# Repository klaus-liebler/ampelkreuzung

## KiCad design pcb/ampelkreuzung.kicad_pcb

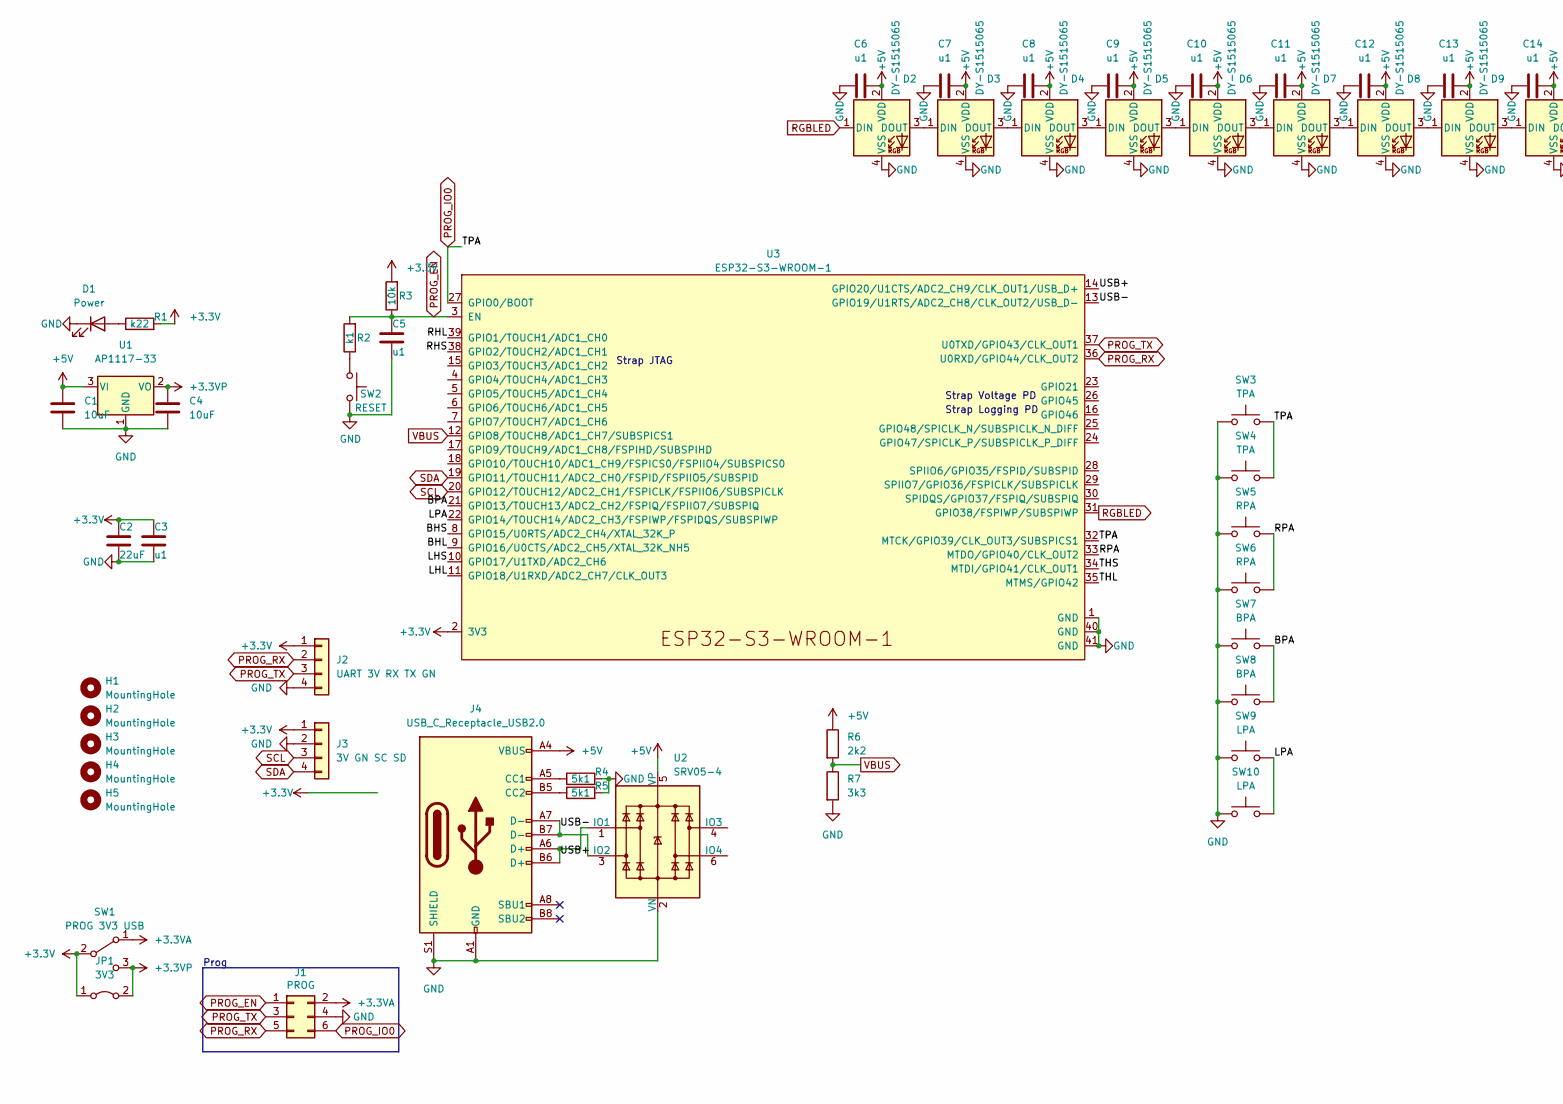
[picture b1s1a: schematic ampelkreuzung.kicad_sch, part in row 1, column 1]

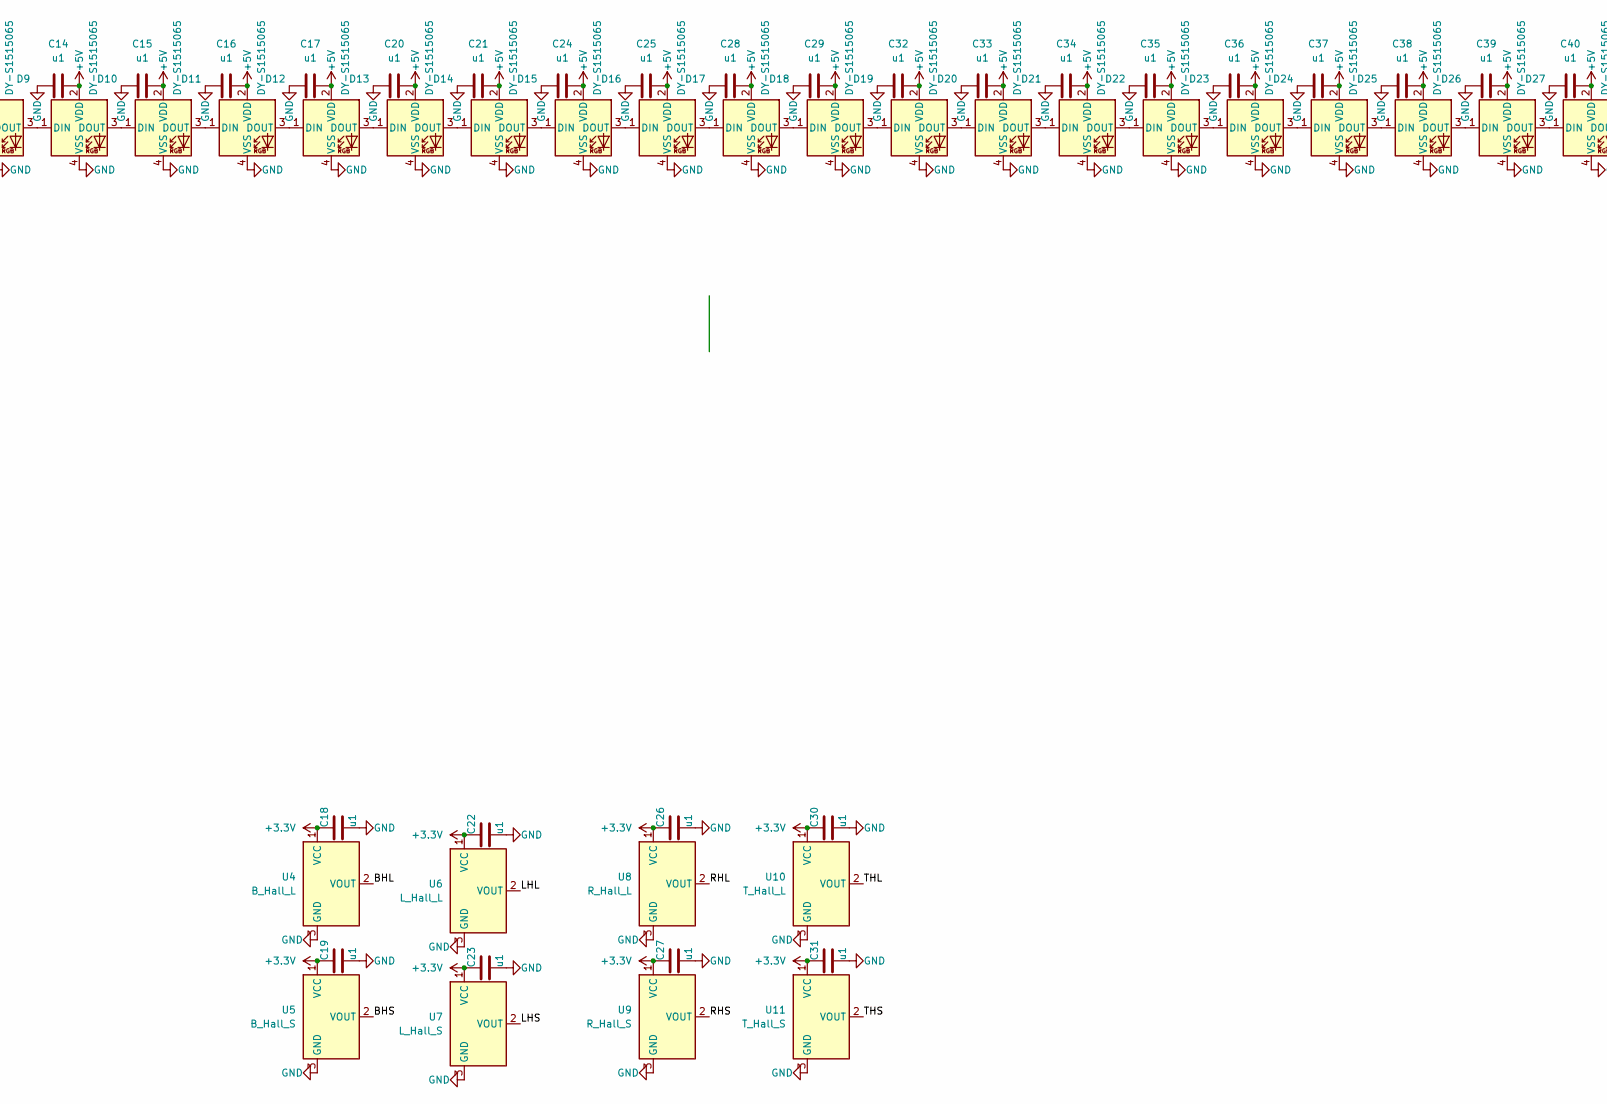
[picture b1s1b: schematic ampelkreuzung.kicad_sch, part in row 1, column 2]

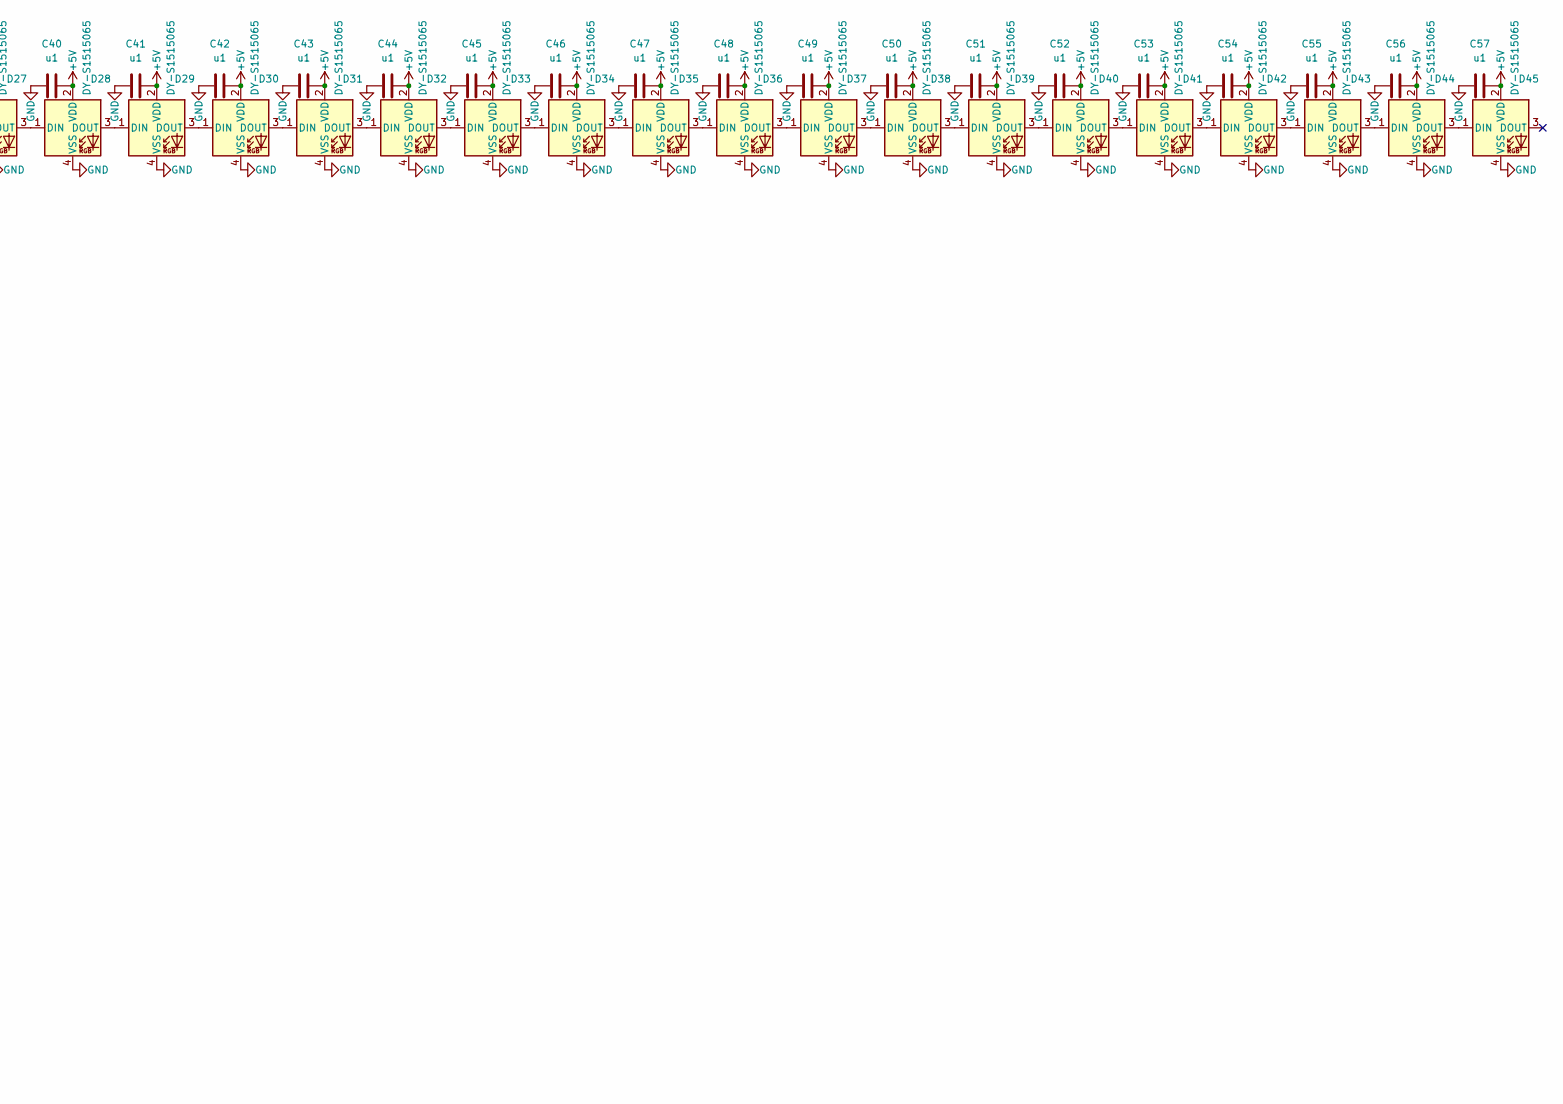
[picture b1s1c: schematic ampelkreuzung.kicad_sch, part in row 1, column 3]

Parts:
C1, C4: 10uF; C_0603_1608Metric
C2: 22uF; C_0603_1608Metric
C3, C5, C6, C7, C8, C9, C10, C11, C12, C13, C14, C15, C16, C17, C18, C19, C20, C21, C22, C23, C24, C25, C26, C27, C28, C29, C30, C31, C32, C33, C34, C35, C36, C37, C38, C39, C40, C41, C42, C43, C44, C45, C46, C47, C48, C49, C50, C51, C52, C53, C54, C55, C56, C57: u1; C_0402_1005Metric
D1: Power; LED_0603_1608Metric
D2, D3, D4, D5, D6, D7, D8, D9, D10, D11, D12, D13, D14, D15, D16, D17, D18, D19, D20, D21, D22, D23, D24, D25, D26, D27, D28, D29, D30, D31, D32, D33, D34, D35, D36, D37, D38, D39, D40, D41, D42, D43, D44, D45: DY-S1515065; LED_0606
H1, H2, H3, H4, H5: MountingHole; MountingHole_3.2mm_M3_DIN965
J1: PROG; IDC_2x03_P1.27mm_Vertical
J2: UART 3V RX TX GN; JST_XH_B4B-XH-A_1x04_P2.50mm_Vertical
J3: 3V GN SC SD; JST_XH_B4B-XH-A_1x04_P2.50mm_Vertical
J4: USB_C_Receptacle_USB2.0; USB_C_Receptacle_HRO_TYPE-C-31-M-12
JP1: 3V3; SolderJumper-2_P1.3mm_Bridged2Bar_RoundedPad1.0x1.5mm
R1: k22; R_0402_1005Metric
R2: k1; R_0402_1005Metric
R3: 10k; R_0402_1005Metric
R4, R5: 5k1; R_0402_1005Metric
R6: 2k2; R_0402_1005Metric
R7: 3k3; R_0402_1005Metric
SW1: PROG 3V3 USB; Switch_SS12D00
SW2: RESET; SW_SPST_TL3342
SW3, SW4: TPA; SW_SPST_TL3342
SW5, SW6: RPA; SW_SPST_TL3342
SW7, SW8: BPA; SW_SPST_TL3342
SW9, SW10: LPA; SW_SPST_TL3342
U1: AP1117-33; SOT-223-3_TabPin2
U2: SRV05-4; SOT-23-6
U3: ESP32-S3-WROOM-1
U4: B_Hall_L; SOT-23_smaller_withoutSilkscreen
U5: B_Hall_S; SOT-23_smaller_withoutSilkscreen
U6: L_Hall_L; SOT-23_smaller_withoutSilkscreen
U7: L_Hall_S; SOT-23_smaller_withoutSilkscreen
U8: R_Hall_L; SOT-23_smaller_withoutSilkscreen
U9: R_Hall_S; SOT-23_smaller_withoutSilkscreen
U10: T_Hall_L; SOT-23_smaller_withoutSilkscreen
U11: T_Hall_S; SOT-23_smaller_withoutSilkscreen

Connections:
+3.3V: C2.1, C3.2, C18.2, C19.2, C22.2, C23.2, C26.2, C27.2, C30.2, C31.2, J2.1, J3.1, JP1.1 (A), R1.2, R3.2, SW1.2 (B), U3.2 (3V3), U4.1 (VCC), U5.1 (VCC), U6.1 (VCC), U7.1 (VCC), U8.1 (VCC), U9.1 (VCC), U10.1 (VCC), U11.1 (VCC)
+3.3VA: J1.2, SW1.1 (A)
+3.3VP: C4.1, JP1.2 (B), SW1.3 (C), U1.2 (VO)
+5V: C1.1, C6.2, C7.2, C8.2, C9.2, C10.2, C11.2, C12.2, C13.2, C14.2, C15.2, C16.2, C17.2, C20.2, C21.2, C24.2, C25.2, C28.2, C29.2, C32.2, C33.2, C34.2, C35.2, C36.2, C37.2, C38.2, C39.2, C40.2, C41.2, C42.2, C43.2, C44.2, C45.2, C46.2, C47.2, C48.2, C49.2, C50.2, C51.2, C52.2, C53.2, C54.2, C55.2, C56.2, C57.2, D2.2 (VDD), D3.2 (VDD), D4.2 (VDD), D5.2 (VDD), D6.2 (VDD), D7.2 (VDD), D8.2 (VDD), D9.2 (VDD), D10.2 (VDD), D11.2 (VDD), D12.2 (VDD), D13.2 (VDD), D14.2 (VDD), D15.2 (VDD), D16.2 (VDD), D17.2 (VDD), D18.2 (VDD), D19.2 (VDD), D20.2 (VDD), D21.2 (VDD), D22.2 (VDD), D23.2 (VDD), D24.2 (VDD), D25.2 (VDD), D26.2 (VDD), D27.2 (VDD), D28.2 (VDD), D29.2 (VDD), D30.2 (VDD), D31.2 (VDD), D32.2 (VDD), D33.2 (VDD), D34.2 (VDD), D35.2 (VDD), D36.2 (VDD), D37.2 (VDD), D38.2 (VDD), D39.2 (VDD), D40.2 (VDD), D41.2 (VDD), D42.2 (VDD), D43.2 (VDD), D44.2 (VDD), D45.2 (VDD), J4.A4 (VBUS), J4.A9 (VBUS), J4.B4 (VBUS), J4.B9 (VBUS), R6.1, U1.3 (VI), U2.5 (VP)
/BHL: U3.9 (GPIO16/U0CTS/ADC2_CH5/XTAL_32K_NH5), U4.2 (VOUT)
/BHS: U3.8 (GPIO15/U0RTS/ADC2_CH4/XTAL_32K_P), U5.2 (VOUT)
/BPA: SW7.2, SW8.2, U3.21 (GPIO13/TOUCH13/ADC2_CH2/FSPIQ/FSPIIO7/S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)
/LHL: U3.11 (GPIO18/U1RXD/ADC2_CH7/CLK_OUT3), U6.2 (VOUT)
/LHS: U3.10 (GPIO17/U1TXD/ADC2_CH6), U7.2 (VOUT)
/LPA: SW9.2, SW10.2, U3.22 (GPIO14/TOUCH14/ADC2_CH3/FSPIWP/FSPIDQS/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)
/RHL: U3.39 (GPIO1/TOUCH1/ADC1_CH0), U8.2 (VOUT)
/RHS: U3.38 (GPIO2/TOUCH2/ADC1_CH1), U9.2 (VOUT)
/RPA: SW5.2, SW6.2, U3.33 (MTDO/GPIO40/CLK_OUT2)
/THL: U3.35 (MTMS/GPIO42), U10.2 (VOUT)
/THS: U3.34 (MTDI/GPIO41/CLK_OUT1), U11.2 (VOUT)
/USB+: J4.A6 (D+), J4.B6 (D+), U2.1 (IO1), U3.14 (GPIO20/U1CTS/ADC2_CH9/CLK_OUT1/USB_D+)
/USB-: J4.A7 (D-), J4.B7 (D-), U2.3 (IO2), U3.13 (GPIO19/U1RTS/ADC2_CH8/CLK_OUT2/USB_D-)
GND: C1.2, C2.2, C3.1, C4.2, C5.2, C6.1, C7.1, C8.1, C9.1, C10.1, C11.1, C12.1, C13.1, C14.1, C15.1, C16.1, C17.1, C18.1, C19.1, C20.1, C21.1, C22.1, C23.1, C24.1, C25.1, C26.1, C27.1, C28.1, C29.1, C30.1, C31.1, C32.1, C33.1, C34.1, C35.1, C36.1, C37.1, C38.1, C39.1, C40.1, C41.1, C42.1, C43.1, C44.1, C45.1, C46.1, C47.1, C48.1, C49.1, C50.1, C51.1, C52.1, C53.1, C54.1, C55.1, C56.1, C57.1, D1.1 (K), D2.4 (VSS), D3.4 (VSS), D4.4 (VSS), D5.4 (VSS), D6.4 (VSS), D7.4 (VSS), D8.4 (VSS), D9.4 (VSS), D10.4 (VSS), D11.4 (VSS), D12.4 (VSS), D13.4 (VSS), D14.4 (VSS), D15.4 (VSS), D16.4 (VSS), D17.4 (VSS), D18.4 (VSS), D19.4 (VSS), D20.4 (VSS), D21.4 (VSS), D22.4 (VSS), D23.4 (VSS), D24.4 (VSS), D25.4 (VSS), D26.4 (VSS), D27.4 (VSS), D28.4 (VSS), D29.4 (VSS), D30.4 (VSS), D31.4 (VSS), D32.4 (VSS), D33.4 (VSS), D34.4 (VSS), D35.4 (VSS), D36.4 (VSS), D37.4 (VSS), D38.4 (VSS), D39.4 (VSS), D40.4 (VSS), D41.4 (VSS), D42.4 (VSS), D43.4 (VSS), D44.4 (VSS), D45.4 (VSS), J1.4, J2.4, J3.2, J4.A1 (GND), J4.A12 (GND), J4.B1 (GND), J4.B12 (GND), J4.S1 (SHIELD), R4.2, R5.2, R7.2, SW2.2, SW3.1, SW4.1, SW5.1, SW6.1, SW7.1, SW8.1, SW9.1, SW10.1, U1.1 (GND), U2.2 (VN), U3.1 (GND), U3.40 (GND), U3.41 (GND), U4.3 (GND), U5.3 (GND), U6.3 (GND), U7.3 (GND), U8.3 (GND), U9.3 (GND), U10.3 (GND), U11.3 (GND)
unnamed: D1.2 (A), R1.1
unnamed: D2.3 (DOUT), D3.1 (DIN)
unnamed: D3.3 (DOUT), D4.1 (DIN)
unnamed: D4.3 (DOUT), D5.1 (DIN)
unnamed: D5.3 (DOUT), D6.1 (DIN)
unnamed: D6.3 (DOUT), D7.1 (DIN)
unnamed: D7.3 (DOUT), D8.1 (DIN)
unnamed: D8.3 (DOUT), D9.1 (DIN)
unnamed: D9.3 (DOUT), D10.1 (DIN)
unnamed: D10.3 (DOUT), D11.1 (DIN)
unnamed: D11.3 (DOUT), D12.1 (DIN)
unnamed: D12.3 (DOUT), D13.1 (DIN)
unnamed: D13.3 (DOUT), D14.1 (DIN)
unnamed: D14.3 (DOUT), D15.1 (DIN)
unnamed: D15.3 (DOUT), D16.1 (DIN)
unnamed: D16.3 (DOUT), D17.1 (DIN)
unnamed: D17.3 (DOUT), D18.1 (DIN)
unnamed: D18.3 (DOUT), D19.1 (DIN)
unnamed: D19.3 (DOUT), D20.1 (DIN)
unnamed: D20.3 (DOUT), D21.1 (DIN)
unnamed: D21.3 (DOUT), D22.1 (DIN)
unnamed: D22.3 (DOUT), D23.1 (DIN)
unnamed: D23.3 (DOUT), D24.1 (DIN)
unnamed: D24.3 (DOUT), D25.1 (DIN)
unnamed: D25.3 (DOUT), D26.1 (DIN)
unnamed: D26.3 (DOUT), D27.1 (DIN)
unnamed: D27.3 (DOUT), D28.1 (DIN)
unnamed: D28.3 (DOUT), D29.1 (DIN)
unnamed: D29.3 (DOUT), D30.1 (DIN)
unnamed: D30.3 (DOUT), D31.1 (DIN)
unnamed: D31.3 (DOUT), D32.1 (DIN)
unnamed: D32.3 (DOUT), D33.1 (DIN)
unnamed: D33.3 (DOUT), D34.1 (DIN)
unnamed: D34.3 (DOUT), D35.1 (DIN)
unnamed: D35.3 (DOUT), D36.1 (DIN)
unnamed: D36.3 (DOUT), D37.1 (DIN)
unnamed: D37.3 (DOUT), D38.1 (DIN)
unnamed: D38.3 (DOUT), D39.1 (DIN)
unnamed: D39.3 (DOUT), D40.1 (DIN)
unnamed: D40.3 (DOUT), D41.1 (DIN)
unnamed: D41.3 (DOUT), D42.1 (DIN)
unnamed: D42.3 (DOUT), D43.1 (DIN)
unnamed: D43.3 (DOUT), D44.1 (DIN)
unnamed: D44.3 (DOUT), D45.1 (DIN)
unnamed: J4.A5 (CC1), R4.1
unnamed: J4.B5 (CC2), R5.1
unnamed: R2.1, SW2.1
PROG_EN: C5.1, J1.1, R2.2, R3.1, U3.3 (EN)
PROG_IO0: J1.6, SW3.2, SW4.2, U3.27 (GPIO0/BOOT), U3.32 (MTCK/GPIO39/CLK_OUT3/SUBSPICS1)
PROG_RX: J1.5, J2.2, U3.36 (U0RXD/GPIO44/CLK_OUT2)
PROG_TX: J1.3, J2.3, U3.37 (U0TXD/GPIO43/CLK_OUT1)
RGBLED: D2.1 (DIN), U3.31 (GPIO38/FSPIWP/SUBSPIWP)
SCL: J3.3, U3.20 (GPIO12/TOUCH12/ADC2_CH1/FSPICLK/FSPIIO6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)
SDA: J3.4, U3.19 (GPIO11/TOUCH11/ADC2_CH0/FSPID/FSPIIO5/S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)
VBUS: R6.2, R7.1, U3.12 (GPIO8/TOUCH8/ADC1_CH7/SUBSPICS1)

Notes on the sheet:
Strap Voltage PD
Strap JTAG
Prog
Strap Logging PD

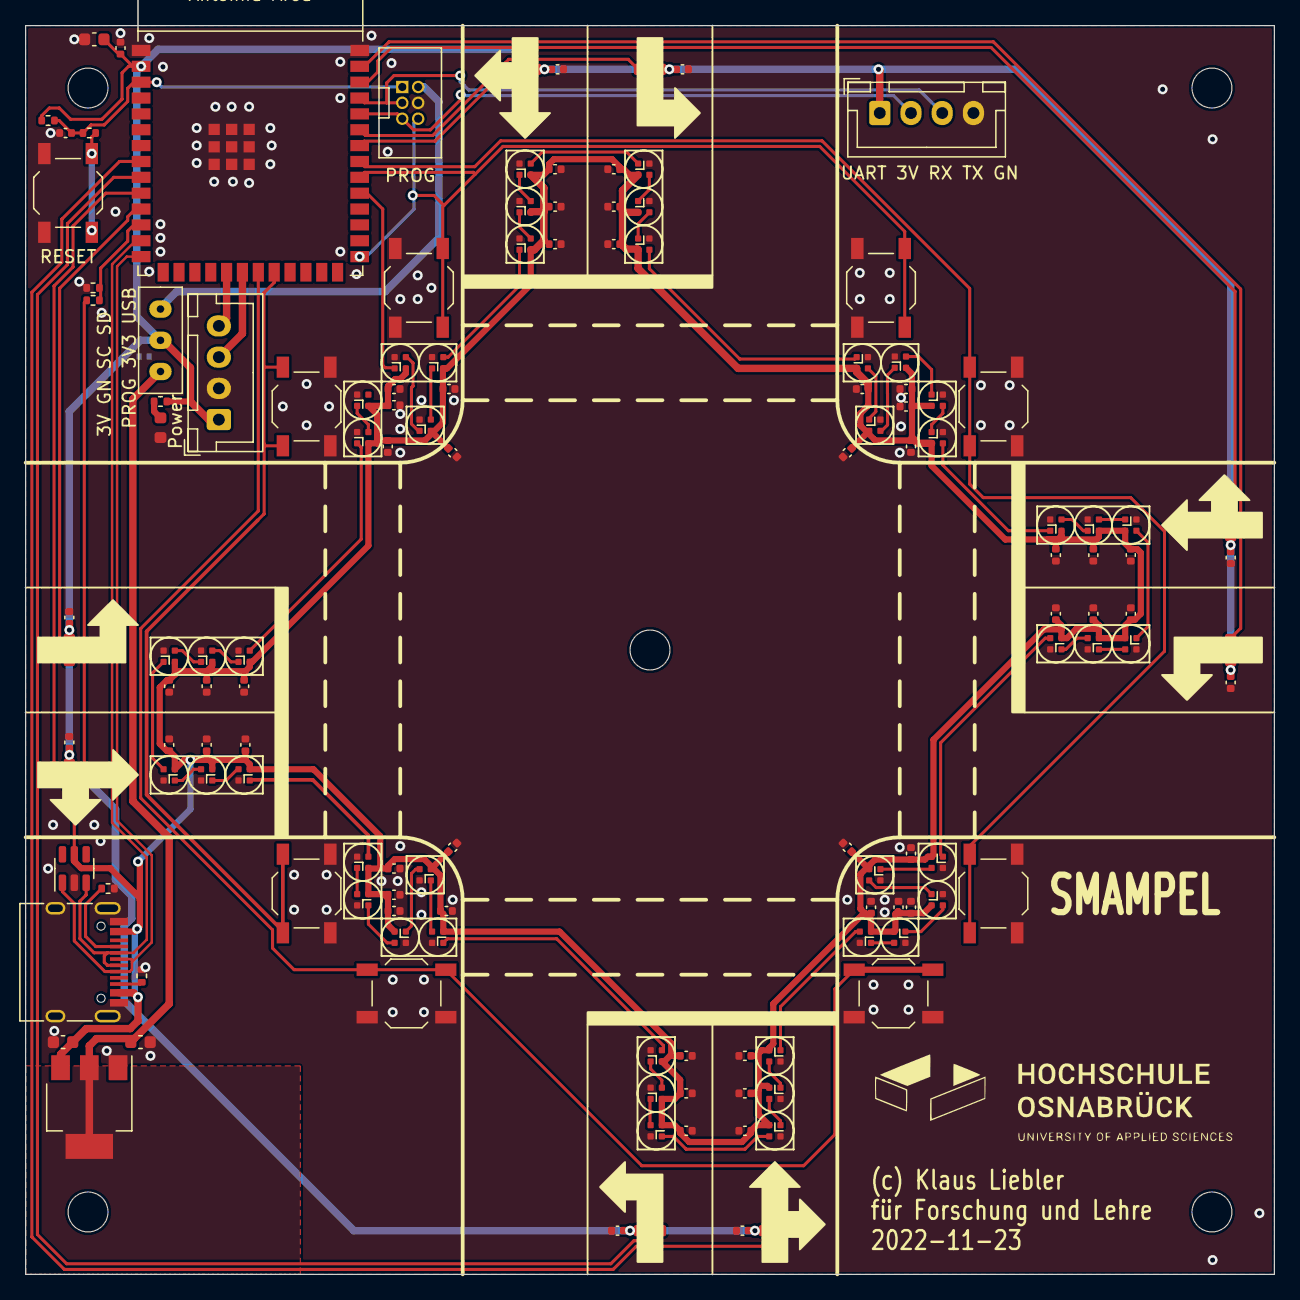
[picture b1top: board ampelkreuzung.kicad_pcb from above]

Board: 2 copper layers, 100.0 x 100.0 mm, 140 parts (1 on the bottom side), 73 nets.

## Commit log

2022-12-08 Webflash
2022-12-08 rename
2022-12-11 Improved Web Flash
2025-03-10 Minors
